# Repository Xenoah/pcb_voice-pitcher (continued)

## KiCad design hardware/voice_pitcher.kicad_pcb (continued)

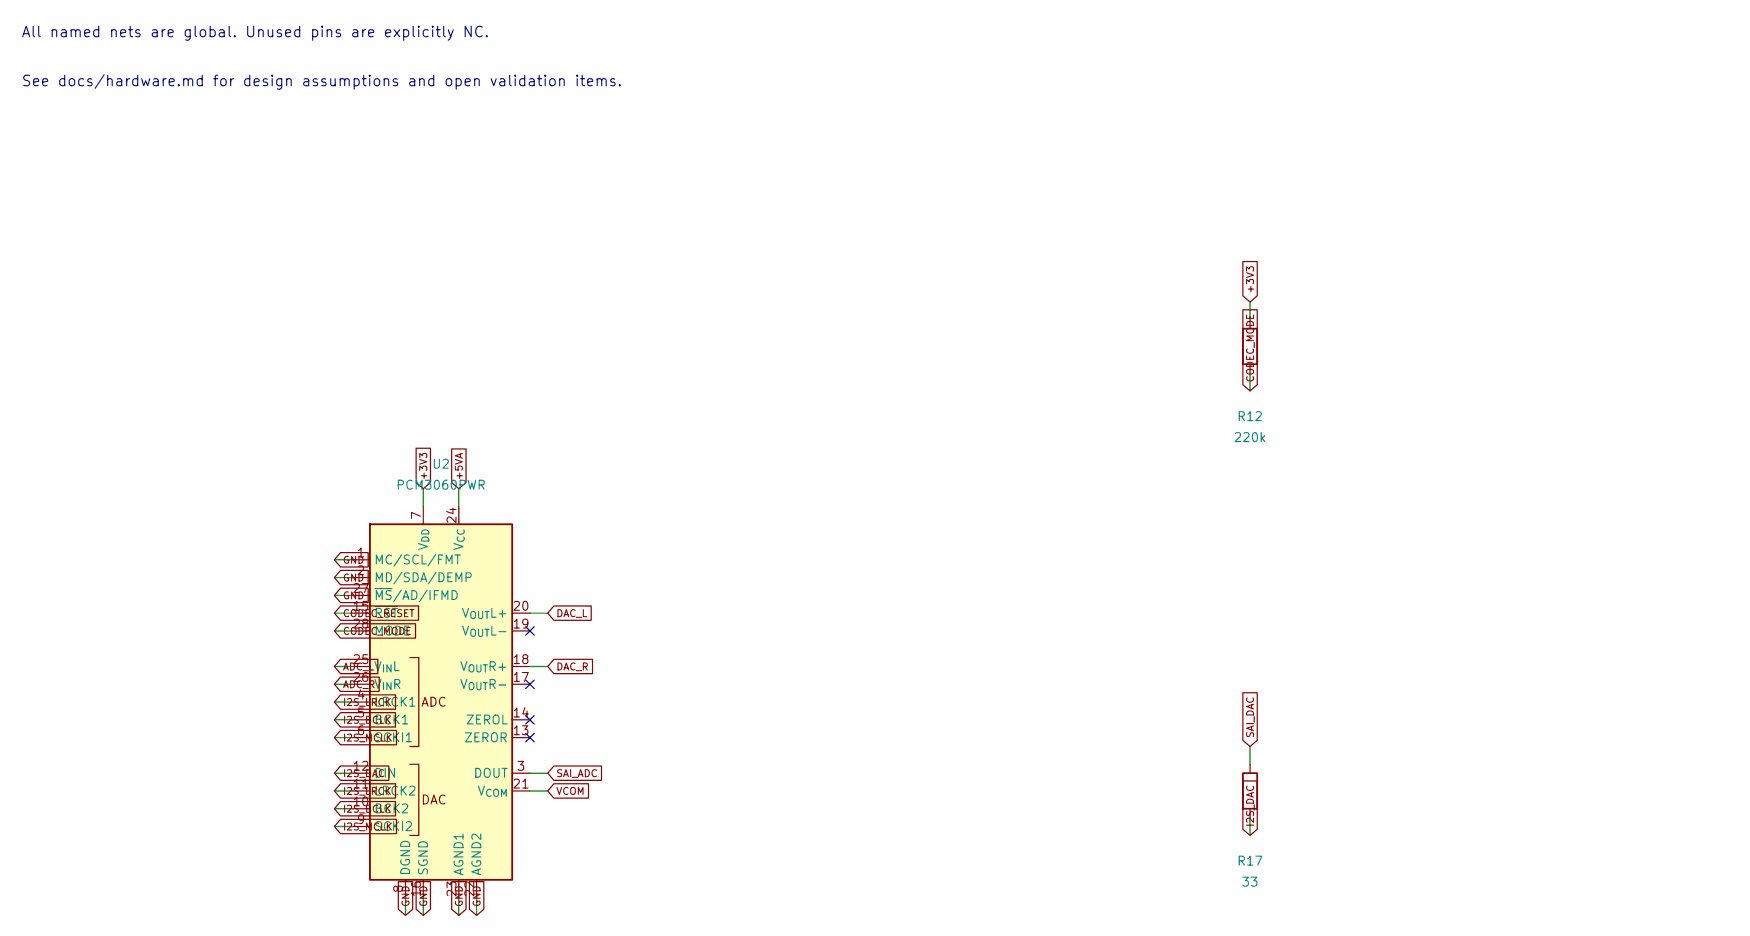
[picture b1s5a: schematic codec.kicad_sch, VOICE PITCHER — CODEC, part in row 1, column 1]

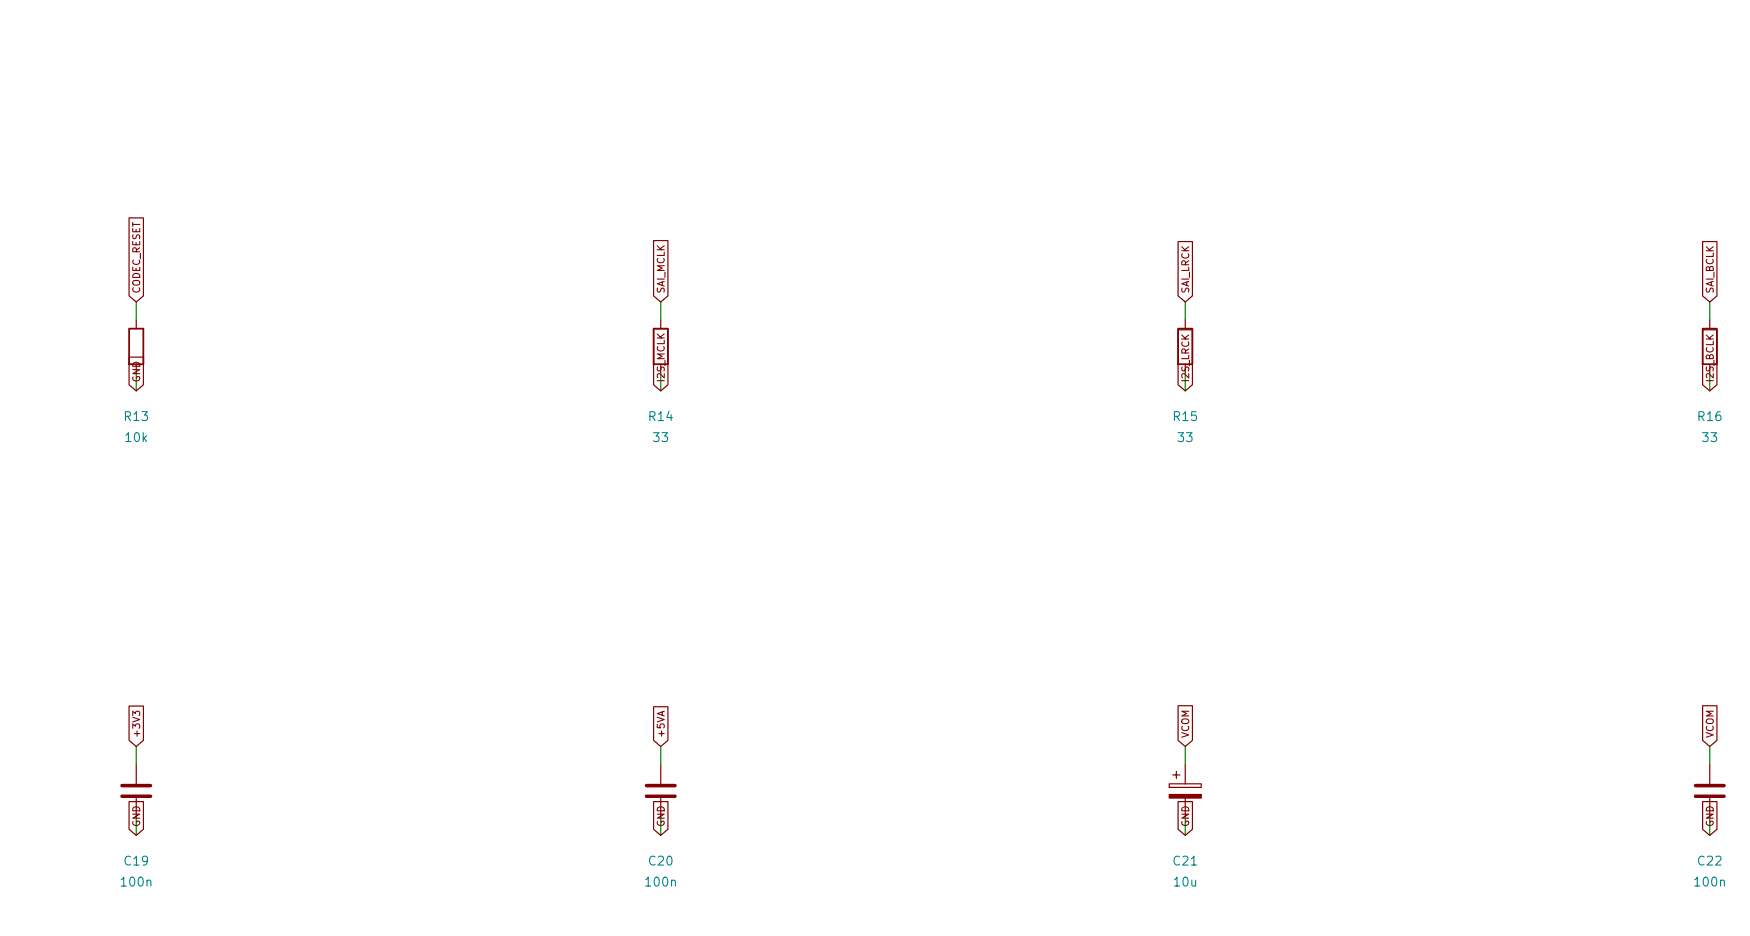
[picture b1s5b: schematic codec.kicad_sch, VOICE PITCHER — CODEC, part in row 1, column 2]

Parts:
C19, C20, C22: 100n; Capacitor_SMD__C_0603_1608Metric; MPN CC0603KRX7R9BB104; LCSC C14663
C21: 10u; Capacitor_SMD__CP_Elec_4x5.8; MPN UWT1C100MCL1GB
R12: 220k; Resistor_SMD__R_0603_1608Metric; MPN 0603WAF2203T5E; LCSC C22961
R13: 10k; Resistor_SMD__R_0603_1608Metric; MPN 0603WAF1002T5E; LCSC C25804
R14, R15, R16, R17: 33; Resistor_SMD__R_0603_1608Metric; MPN 0603WAF330JT5E; LCSC C23140
U2: PCM3060PWR; Package_SO__TSSOP-28_4.4x9.7mm_P0.65mm; MPN PCM3060PWR; LCSC C2651841

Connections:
+3V3: C19.1, R12.1, U2.7 (V_{DD}); also elsewhere on the board
+5VA: C20.1, U2.24 (V_{CC}); also elsewhere on the board
ADC_L: U2.25 (V_{IN}L); also elsewhere on the board
ADC_R: U2.26 (V_{IN}R); also elsewhere on the board
CODEC_MODE: R12.2, U2.28 (MODE)
CODEC_RESET: R13.1, U2.15 (~RST); also elsewhere on the board
DAC_L: U2.20 (V_{OUT}L+); also elsewhere on the board
DAC_R: U2.18 (V_{OUT}R+); also elsewhere on the board
GND: C19.2, C20.2, C21.2, C22.2, R13.2, U2.1 (MC/SCL/FMT), U2.2 (MD/SDA/DEMP), U2.8 (DGND), U2.16 (SGND), U2.22 (AGND2), U2.23 (AGND1), U2.27 (~MS/AD/IFMD); also elsewhere on the board
I2S_BCLK: R16.2, U2.5 (BCK1), U2.10 (BCK2)
I2S_DAC: R17.2, U2.12 (DIN)
I2S_LRCK: R15.2, U2.4 (LRCK1), U2.11 (LRCK2)
I2S_MCLK: R14.2, U2.6 (SCKI1), U2.9 (SCKI2)
SAI_ADC: U2.3 (DOUT); also elsewhere on the board
SAI_BCLK: R16.1; also elsewhere on the board
SAI_DAC: R17.1; also elsewhere on the board
SAI_LRCK: R15.1; also elsewhere on the board
SAI_MCLK: R14.1; also elsewhere on the board
VCOM: C21.1, C22.1, U2.21 (V_{COM}); also elsewhere on the board

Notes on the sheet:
All named nets are global. Unused pins are explicitly NC.
See docs/hardware.md for design assumptions and open validation items.

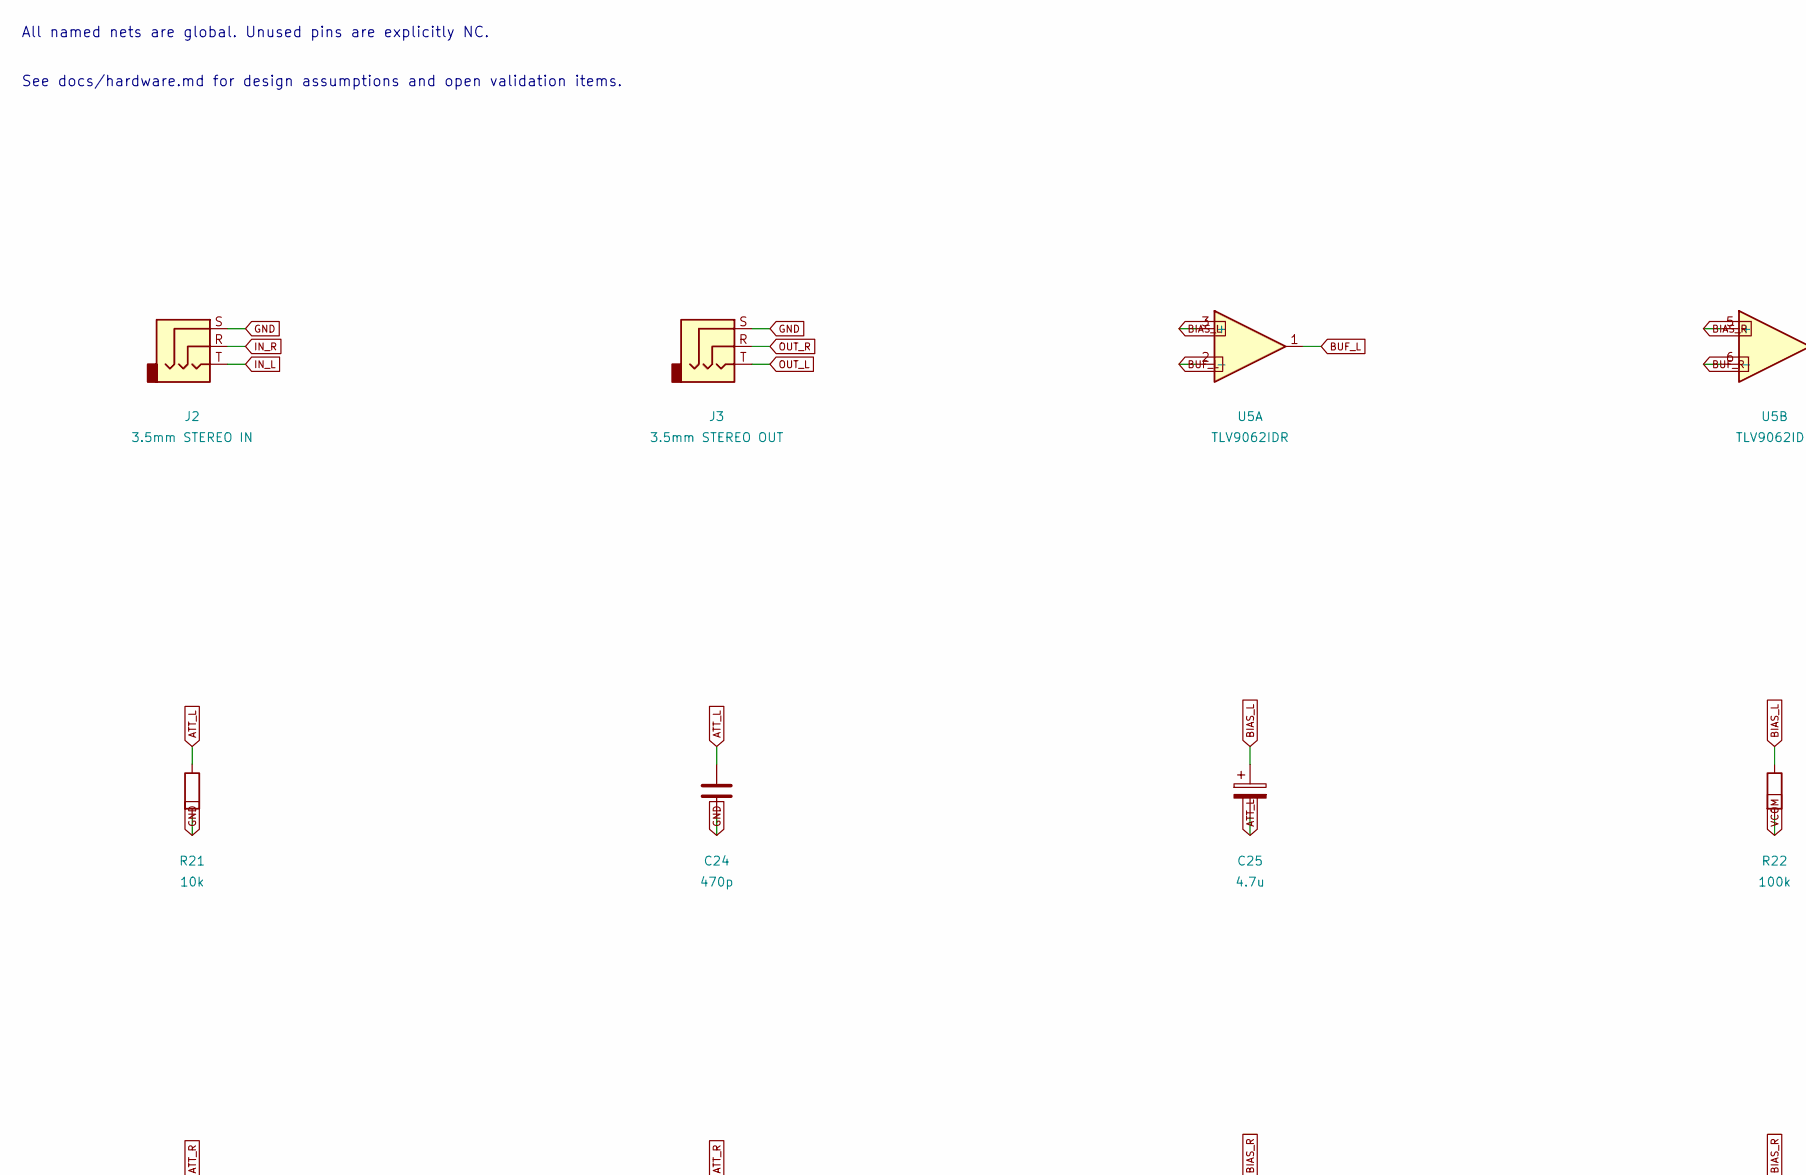
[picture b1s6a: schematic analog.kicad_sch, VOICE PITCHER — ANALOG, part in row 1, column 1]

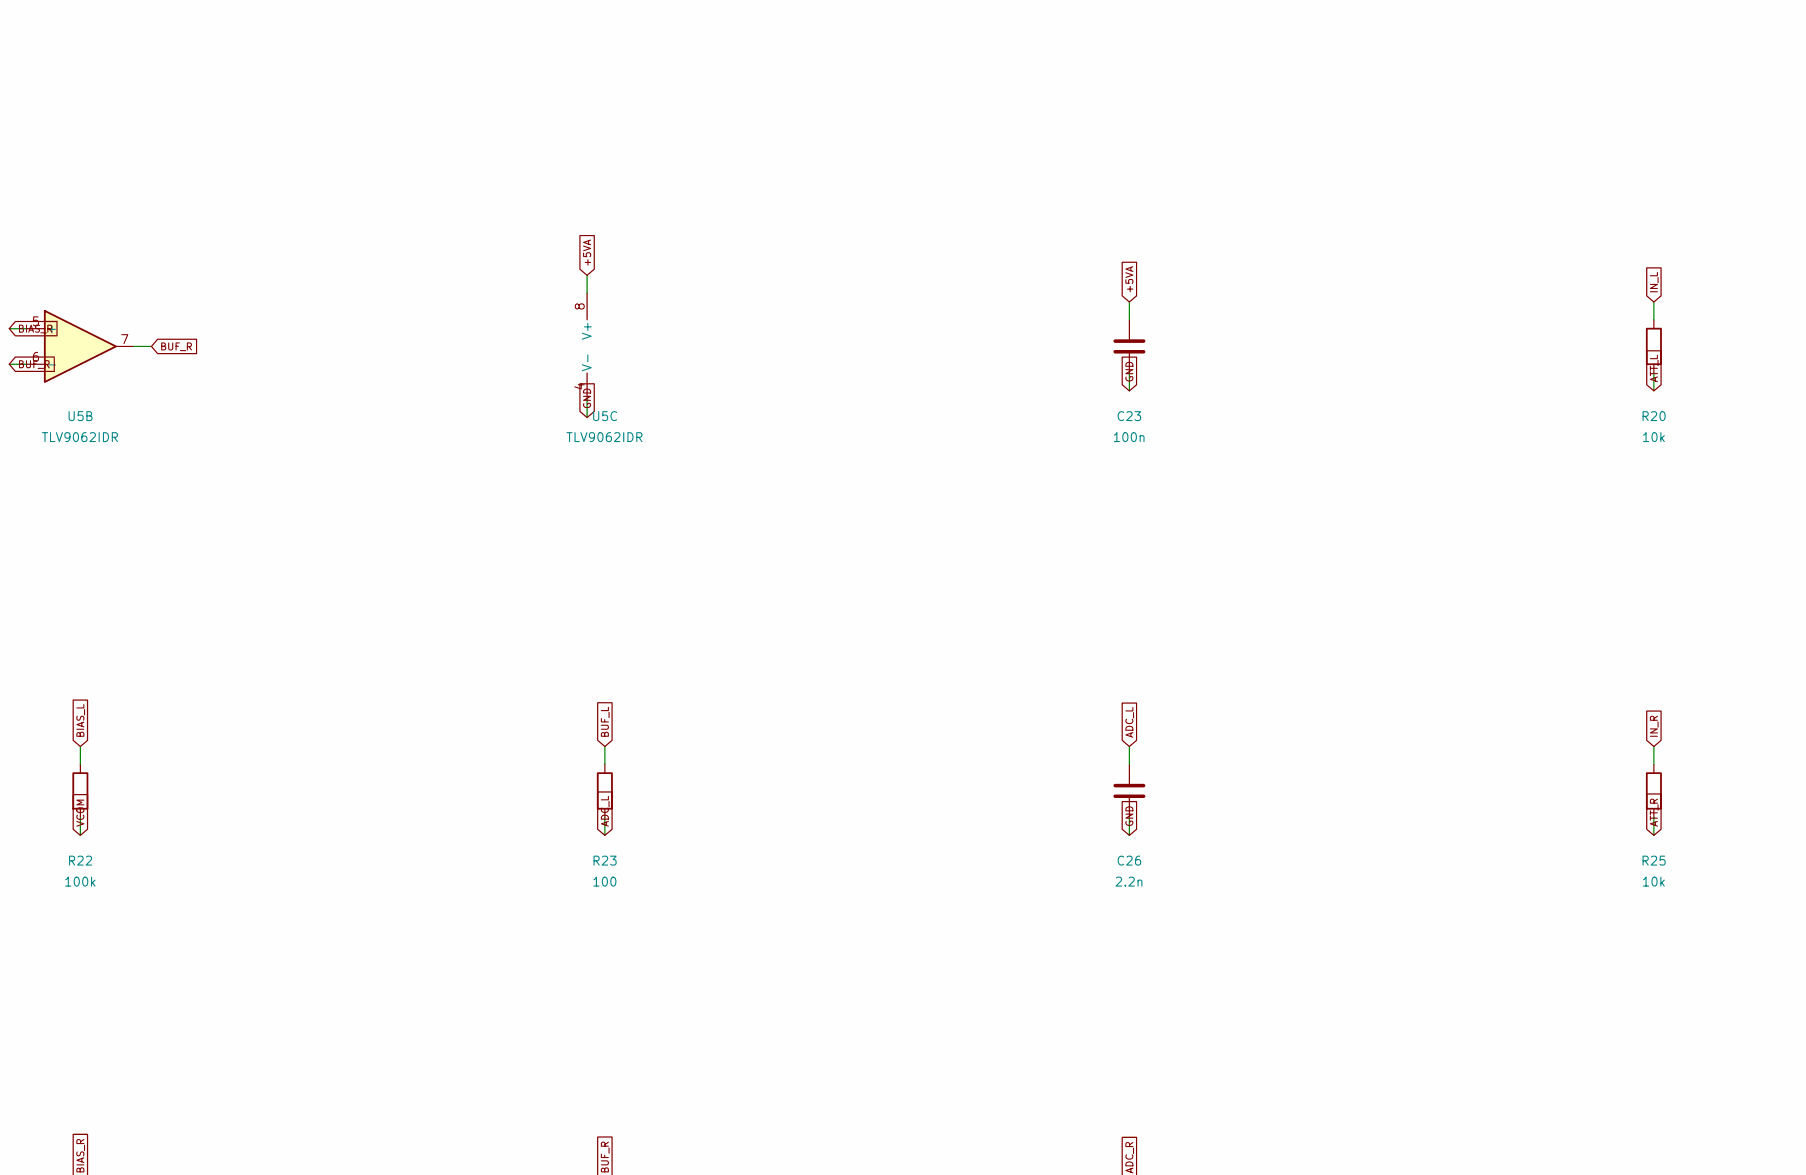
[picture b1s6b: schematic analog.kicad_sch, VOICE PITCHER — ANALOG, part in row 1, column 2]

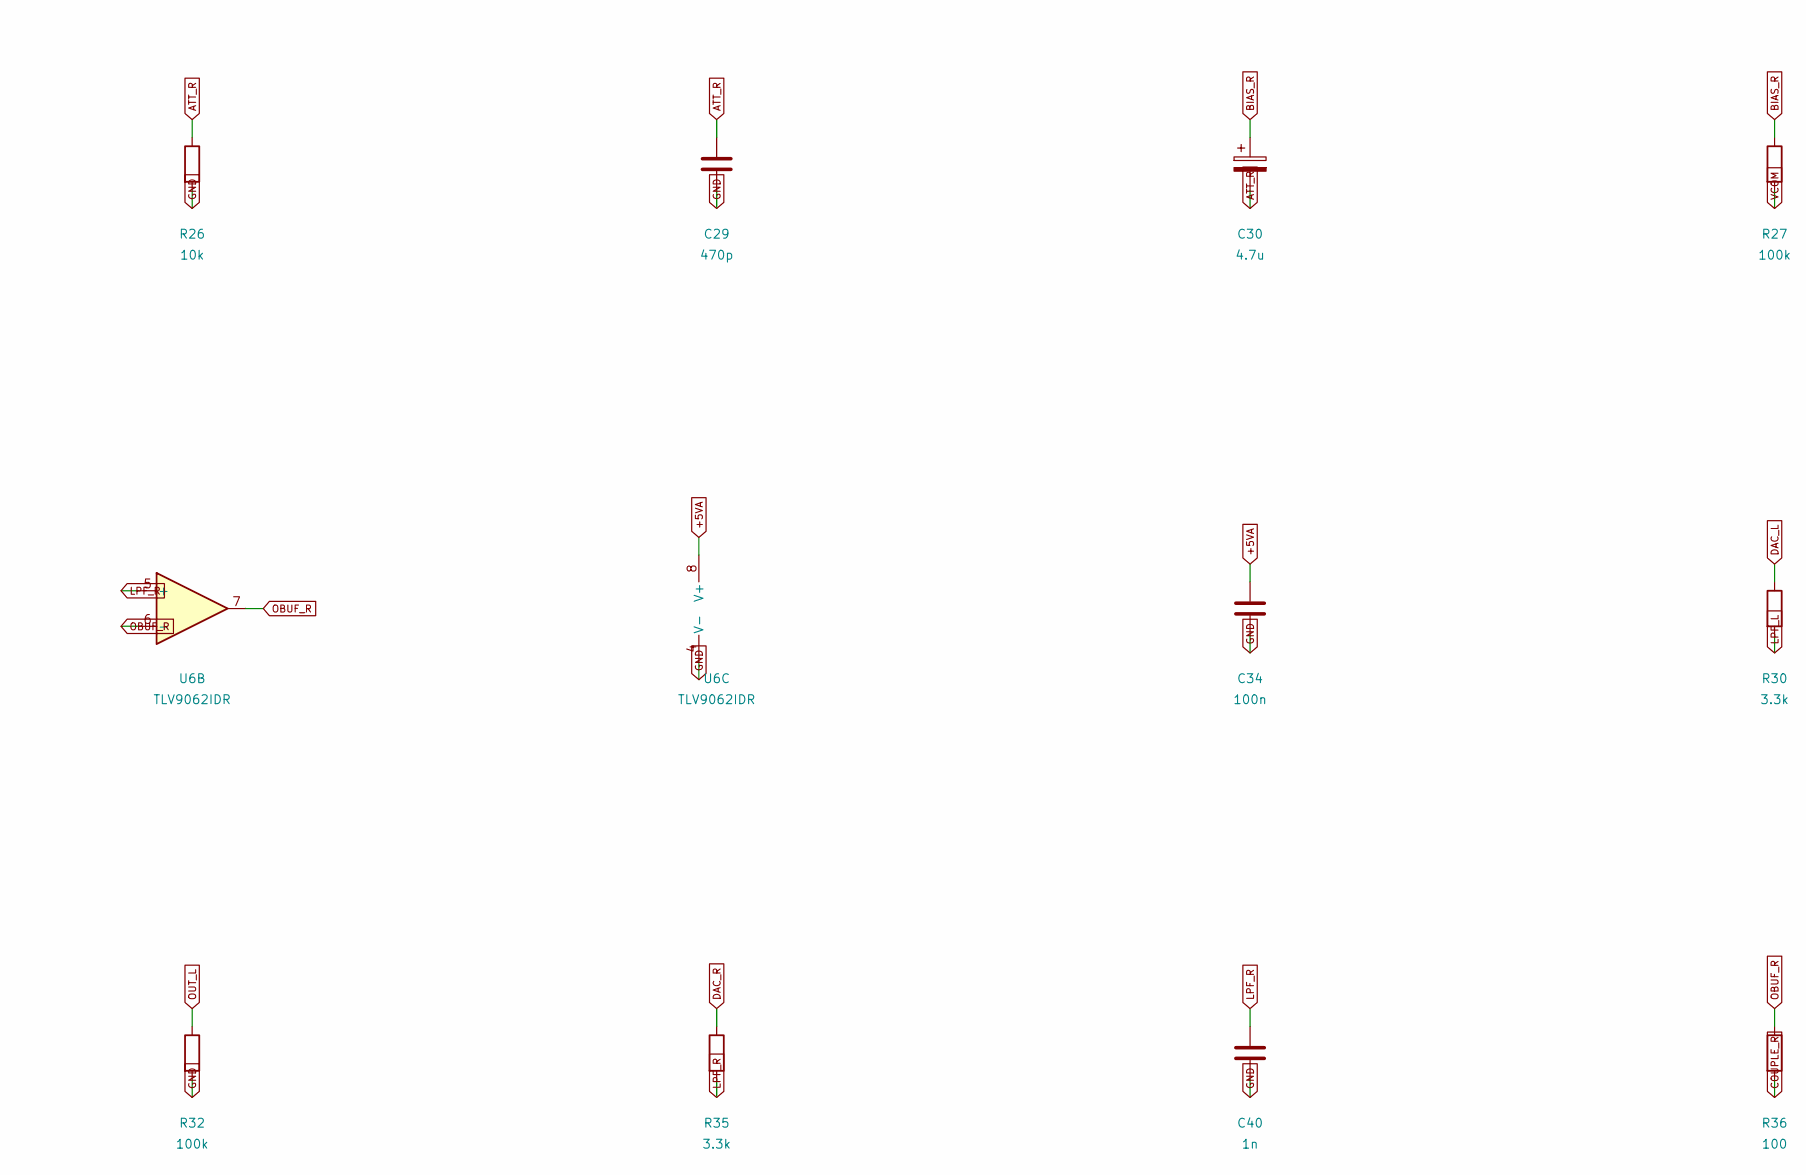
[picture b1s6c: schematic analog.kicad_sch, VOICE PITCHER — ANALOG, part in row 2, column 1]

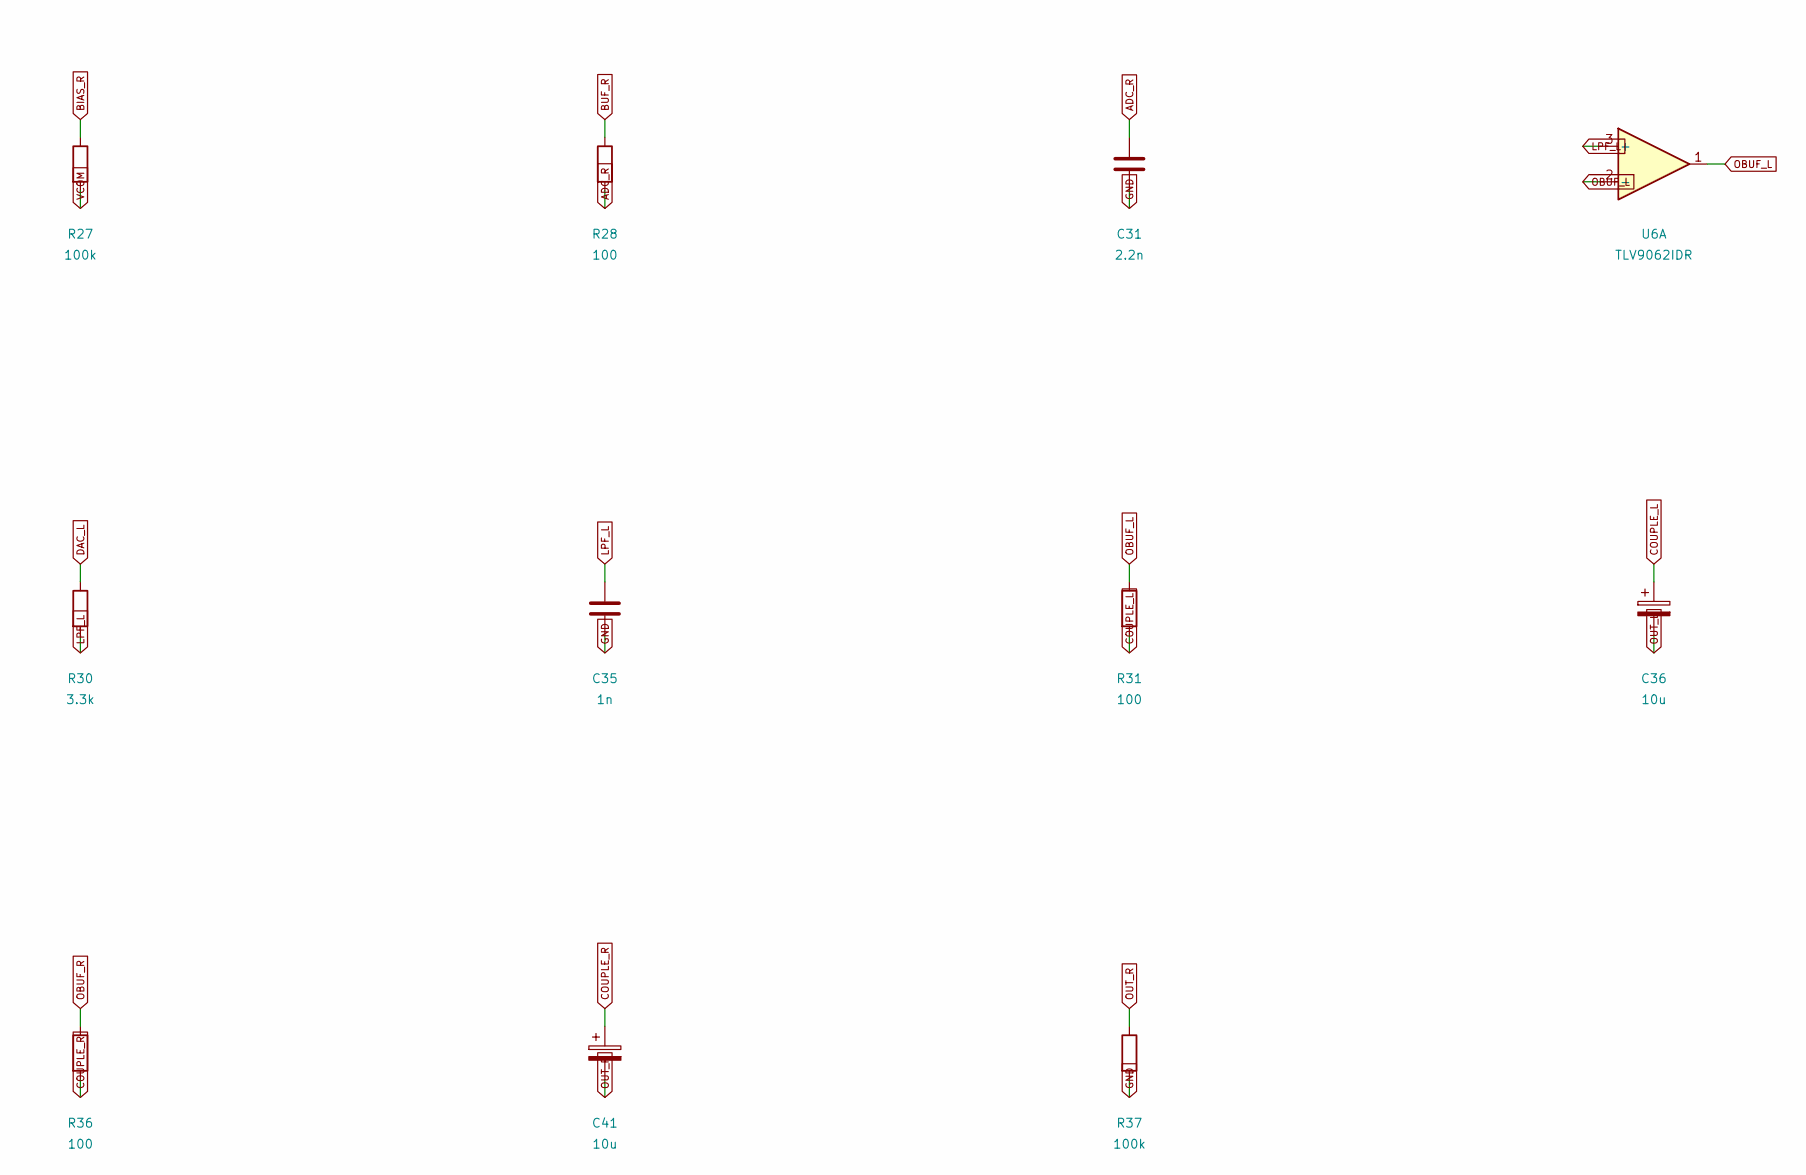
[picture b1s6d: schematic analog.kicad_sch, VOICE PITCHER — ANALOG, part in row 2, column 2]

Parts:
C23, C34: 100n; Capacitor_SMD__C_0603_1608Metric; MPN CC0603KRX7R9BB104; LCSC C14663
C24, C29: 470p; Capacitor_SMD__C_0603_1608Metric; MPN GRM1885C1H471JA01D
C25, C30: 4.7u; Capacitor_SMD__CP_Elec_4x5.8; MPN UWT1C4R7MCL1GB
C26, C31: 2.2n; Capacitor_SMD__C_0603_1608Metric; MPN GRM1885C1H222JA01D
C35, C40: 1n; Capacitor_SMD__C_0603_1608Metric; MPN GRM1885C1H102JA01D
C36, C41: 10u; Capacitor_SMD__CP_Elec_4x5.8; MPN UWT1C100MCL1GB
J2: 3.5mm STEREO IN; Connector_Audio__Jack_3.5mm_CUI_SJ-3523-SMT_Horizontal; MPN SJ-3523-SMT-TR
J3: 3.5mm STEREO OUT; Connector_Audio__Jack_3.5mm_CUI_SJ-3523-SMT_Horizontal; MPN SJ-3523-SMT-TR
R20, R21, R25, R26: 10k; Resistor_SMD__R_0603_1608Metric; MPN 0603WAF1002T5E; LCSC C25804
R22, R27, R32, R37: 100k; Resistor_SMD__R_0603_1608Metric; MPN 0603WAF1003T5E; LCSC C25803
R23, R28, R31, R36: 100; Resistor_SMD__R_0603_1608Metric; MPN 0603WAF1000T5E; LCSC C22775
R30, R35: 3.3k; Resistor_SMD__R_0603_1608Metric; MPN 0603WAF3301T5E; LCSC C22978
U5, U6: TLV9062IDR; Package_SO__SOIC-8_3.9x4.9mm_P1.27mm; MPN TLV9062IDR

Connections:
+5VA: C23.1, C34.1, U5.8 (V+), U6.8 (V+); also elsewhere on the board
ADC_L: C26.1, R23.2; also elsewhere on the board
ADC_R: C31.1, R28.2; also elsewhere on the board
ATT_L: C24.1, C25.2, R20.2, R21.1
ATT_R: C29.1, C30.2, R25.2, R26.1
BIAS_L: C25.1, R22.1, U5.3 (+)
BIAS_R: C30.1, R27.1, U5.5 (+)
BUF_L: R23.1, U5.1, U5.2 (-)
BUF_R: R28.1, U5.6 (-), U5.7
COUPLE_L: C36.1, R31.2
COUPLE_R: C41.1, R36.2
DAC_L: R30.1; also elsewhere on the board
DAC_R: R35.1; also elsewhere on the board
GND: C23.2, C24.2, C26.2, C29.2, C31.2, C34.2, C35.2, C40.2, J2.S, J3.S, R21.2, R26.2, R32.2, R37.2, U5.4 (V-), U6.4 (V-); also elsewhere on the board
IN_L: J2.T, R20.1
IN_R: J2.R, R25.1
LPF_L: C35.1, R30.2, U6.3 (+)
LPF_R: C40.1, R35.2, U6.5 (+)
OBUF_L: R31.1, U6.1, U6.2 (-)
OBUF_R: R36.1, U6.6 (-), U6.7
OUT_L: C36.2, J3.T, R32.1
OUT_R: C41.2, J3.R, R37.1
VCOM: R22.2, R27.2; also elsewhere on the board

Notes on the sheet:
All named nets are global. Unused pins are explicitly NC.
See docs/hardware.md for design assumptions and open validation items.

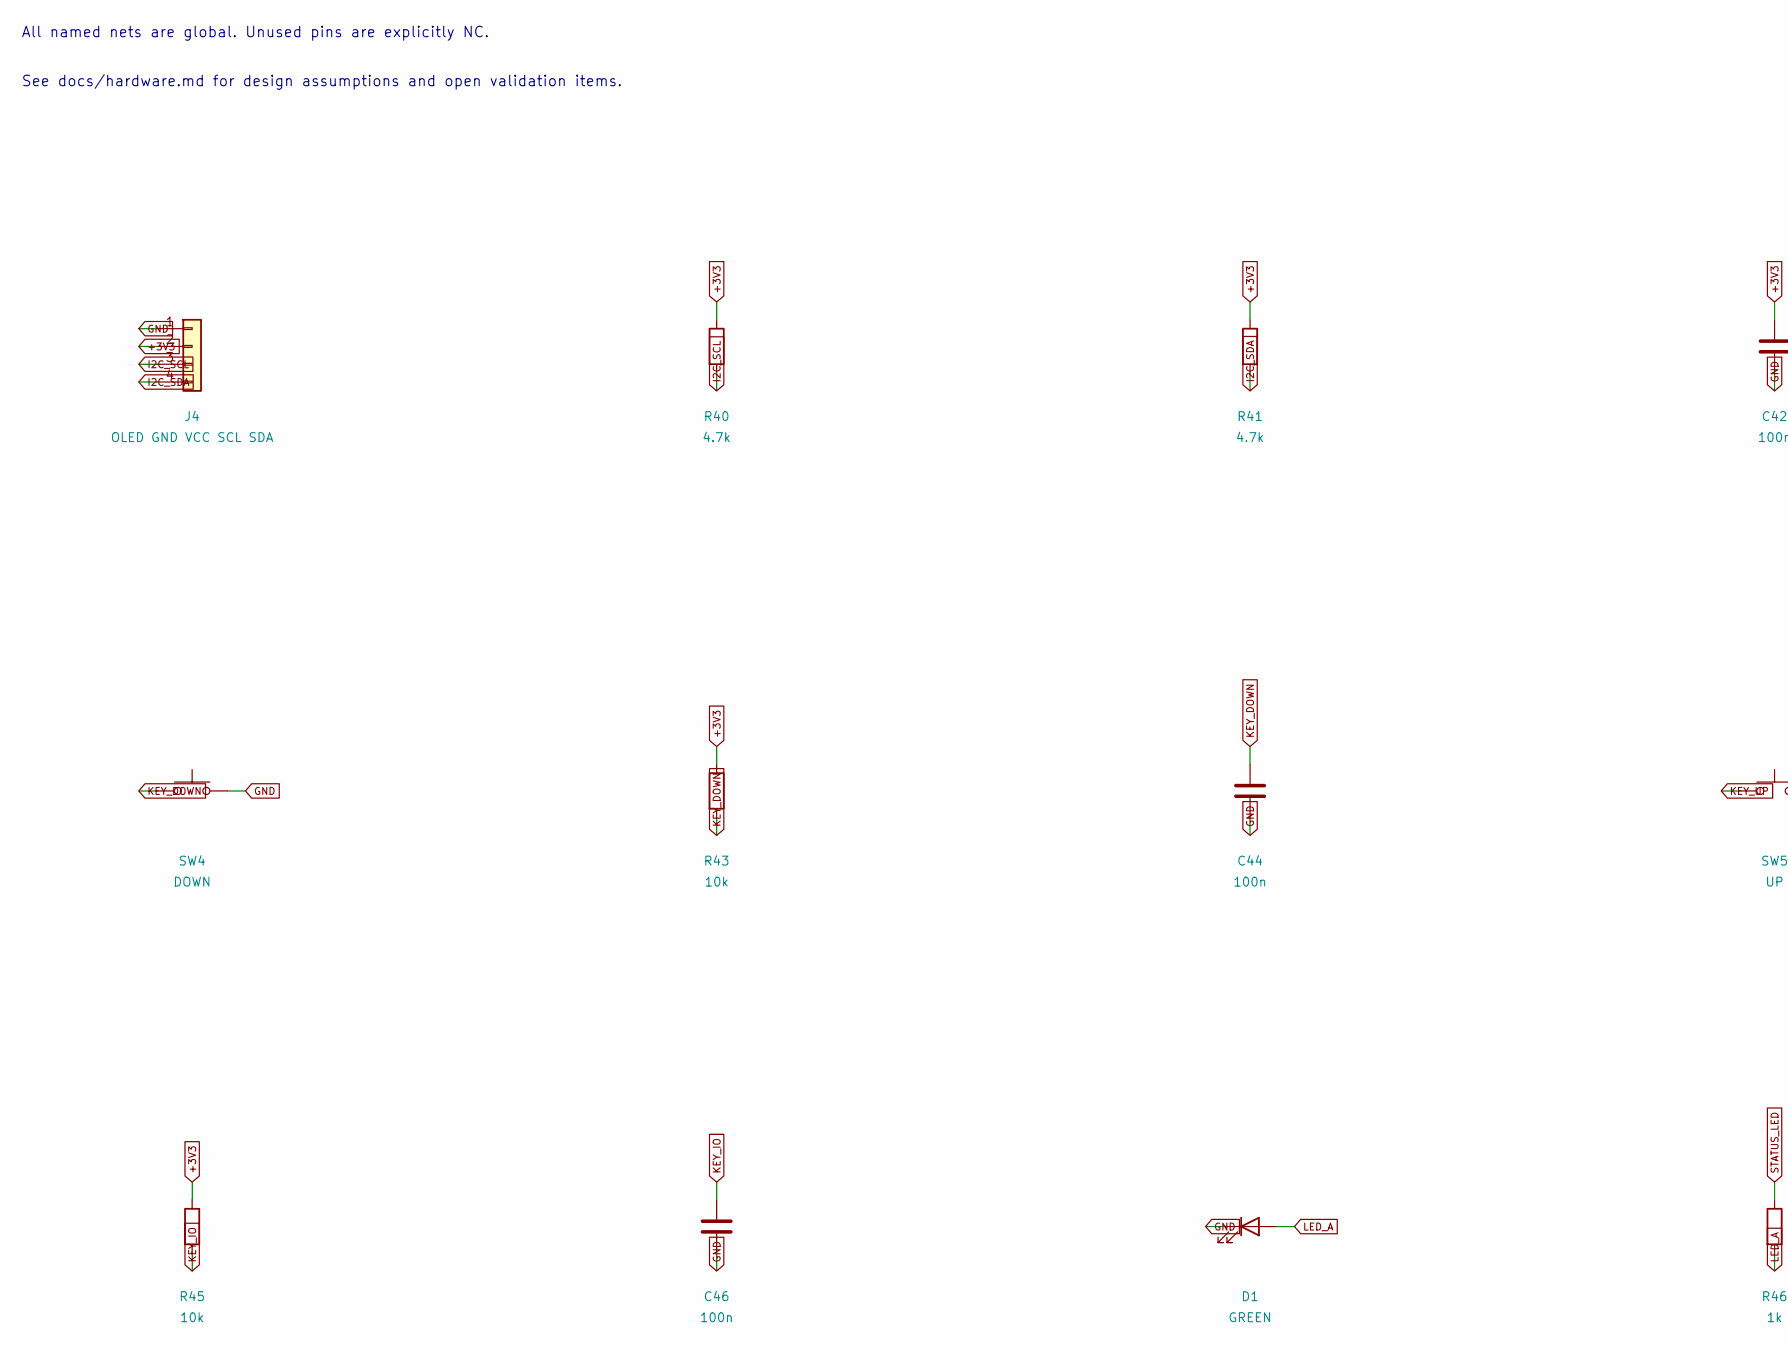
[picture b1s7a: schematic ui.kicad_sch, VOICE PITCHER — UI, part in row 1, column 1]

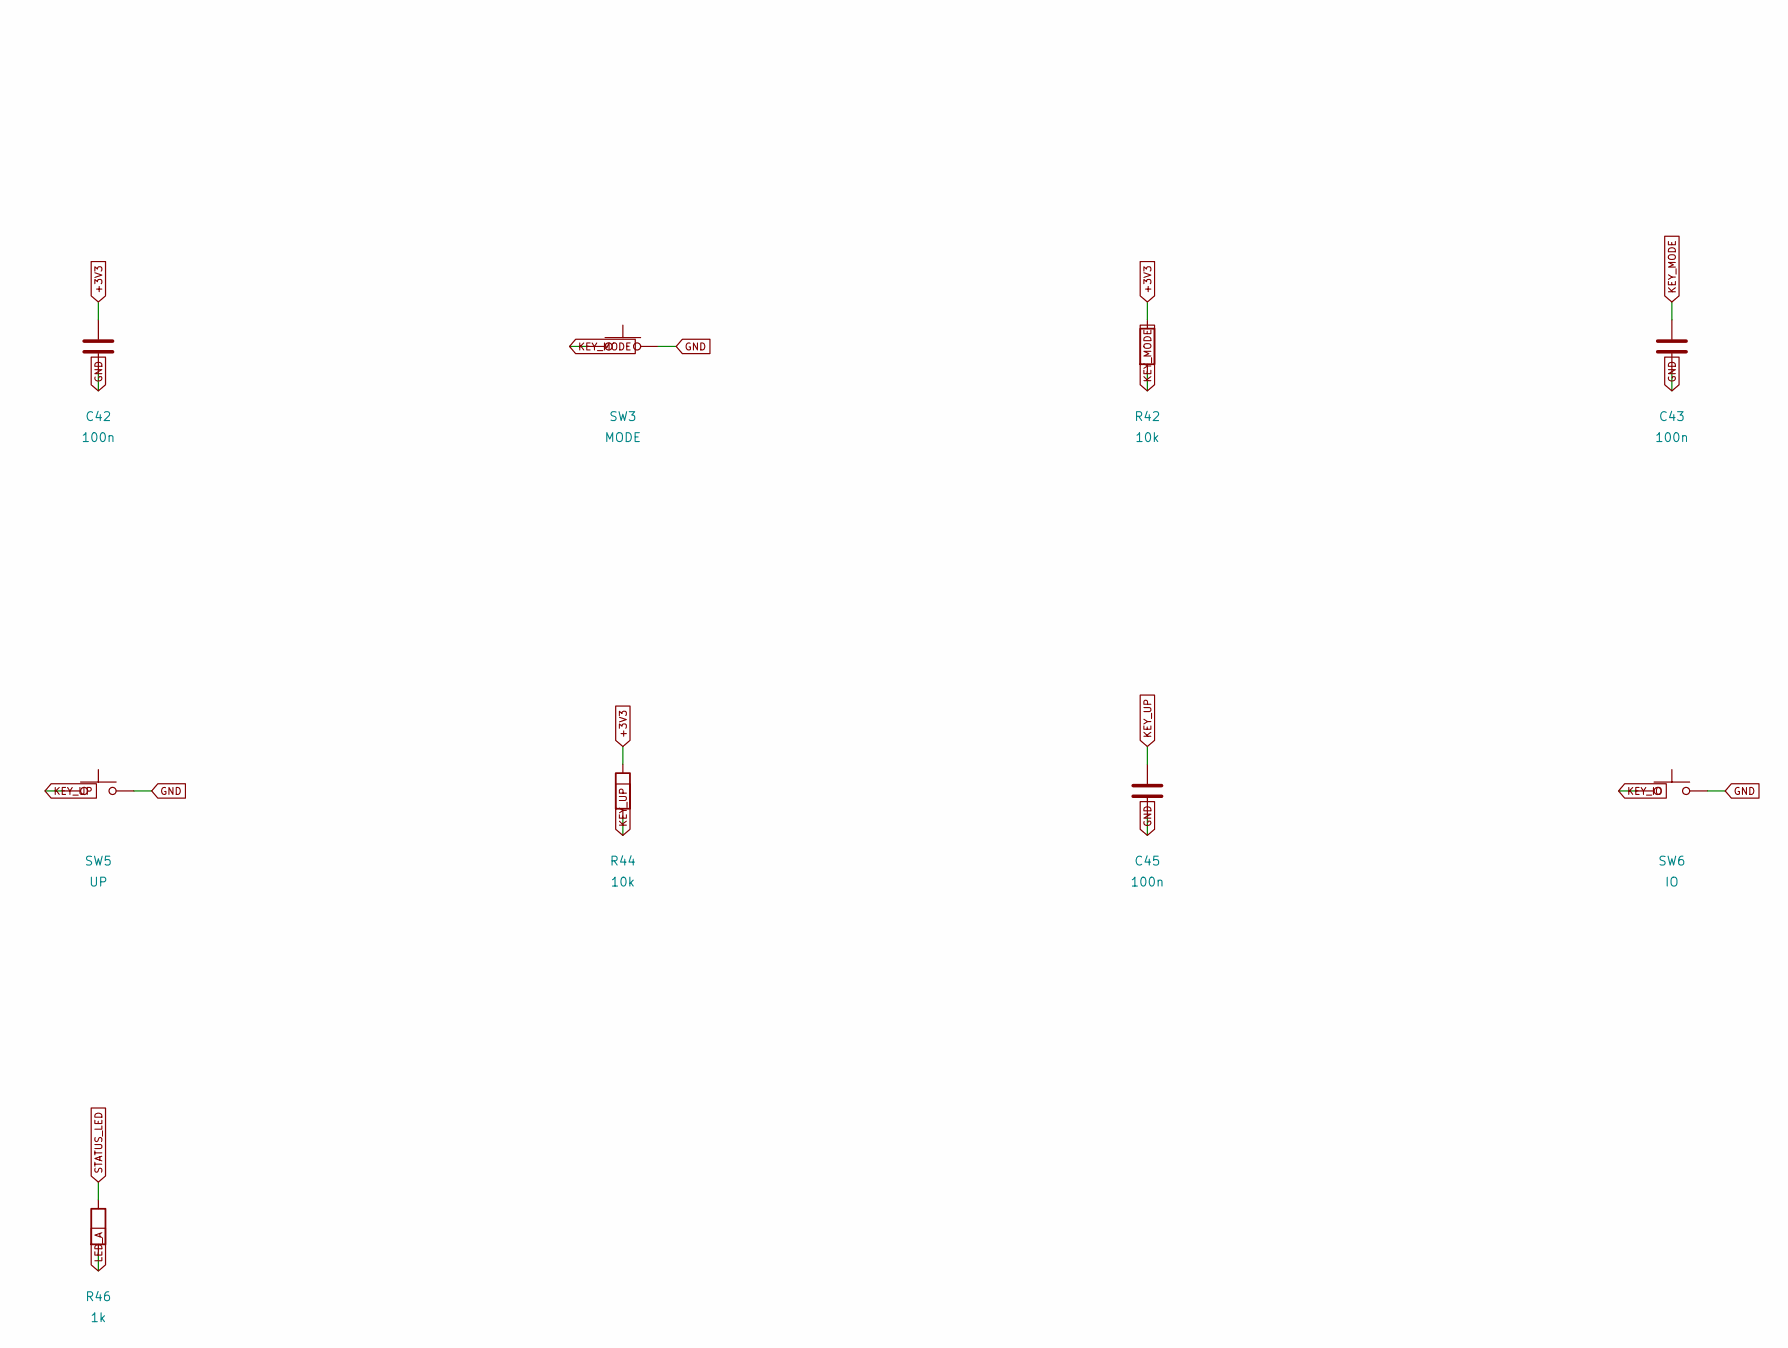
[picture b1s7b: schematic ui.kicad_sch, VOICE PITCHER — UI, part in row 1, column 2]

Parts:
C42, C43, C44, C45, C46: 100n; Capacitor_SMD__C_0603_1608Metric; MPN CC0603KRX7R9BB104; LCSC C14663
D1: GREEN; LED_SMD__LED_0603_1608Metric; MPN LTST-C190KGKT
J4: OLED GND VCC SCL SDA; Connector_PinHeader_2.54mm__PinHeader_1x04_P2.54mm_Vertical; MPN 1x4 2.54mm OLED socket
R40, R41: 4.7k; Resistor_SMD__R_0603_1608Metric; MPN 0603WAF4701T5E; LCSC C23162
R42, R43, R44, R45: 10k; Resistor_SMD__R_0603_1608Metric; MPN 0603WAF1002T5E; LCSC C25804
R46: 1k; Resistor_SMD__R_0603_1608Metric; MPN 0603WAF1001T5E; LCSC C21190
SW3: MODE; Button_Switch_SMD__SW_SPST_TL3342; MPN TL3342F160QG
SW4: DOWN; Button_Switch_SMD__SW_SPST_TL3342; MPN TL3342F160QG
SW5: UP; Button_Switch_SMD__SW_SPST_TL3342; MPN TL3342F160QG
SW6: IO; Button_Switch_SMD__SW_SPST_TL3342; MPN TL3342F160QG

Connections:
+3V3: C42.1, J4.2, R40.1, R41.1, R42.1, R43.1, R44.1, R45.1; also elsewhere on the board
GND: C42.2, C43.2, C44.2, C45.2, C46.2, D1.1 (K), J4.1, SW3.2, SW4.2, SW5.2, SW6.2; also elsewhere on the board
I2C_SCL: J4.3, R40.2; also elsewhere on the board
I2C_SDA: J4.4, R41.2; also elsewhere on the board
KEY_DOWN: C44.1, R43.2, SW4.1; also elsewhere on the board
KEY_IO: C46.1, R45.2, SW6.1; also elsewhere on the board
KEY_MODE: C43.1, R42.2, SW3.1; also elsewhere on the board
KEY_UP: C45.1, R44.2, SW5.1; also elsewhere on the board
LED_A: D1.2 (A), R46.2
STATUS_LED: R46.1; also elsewhere on the board

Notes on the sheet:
All named nets are global. Unused pins are explicitly NC.
See docs/hardware.md for design assumptions and open validation items.
